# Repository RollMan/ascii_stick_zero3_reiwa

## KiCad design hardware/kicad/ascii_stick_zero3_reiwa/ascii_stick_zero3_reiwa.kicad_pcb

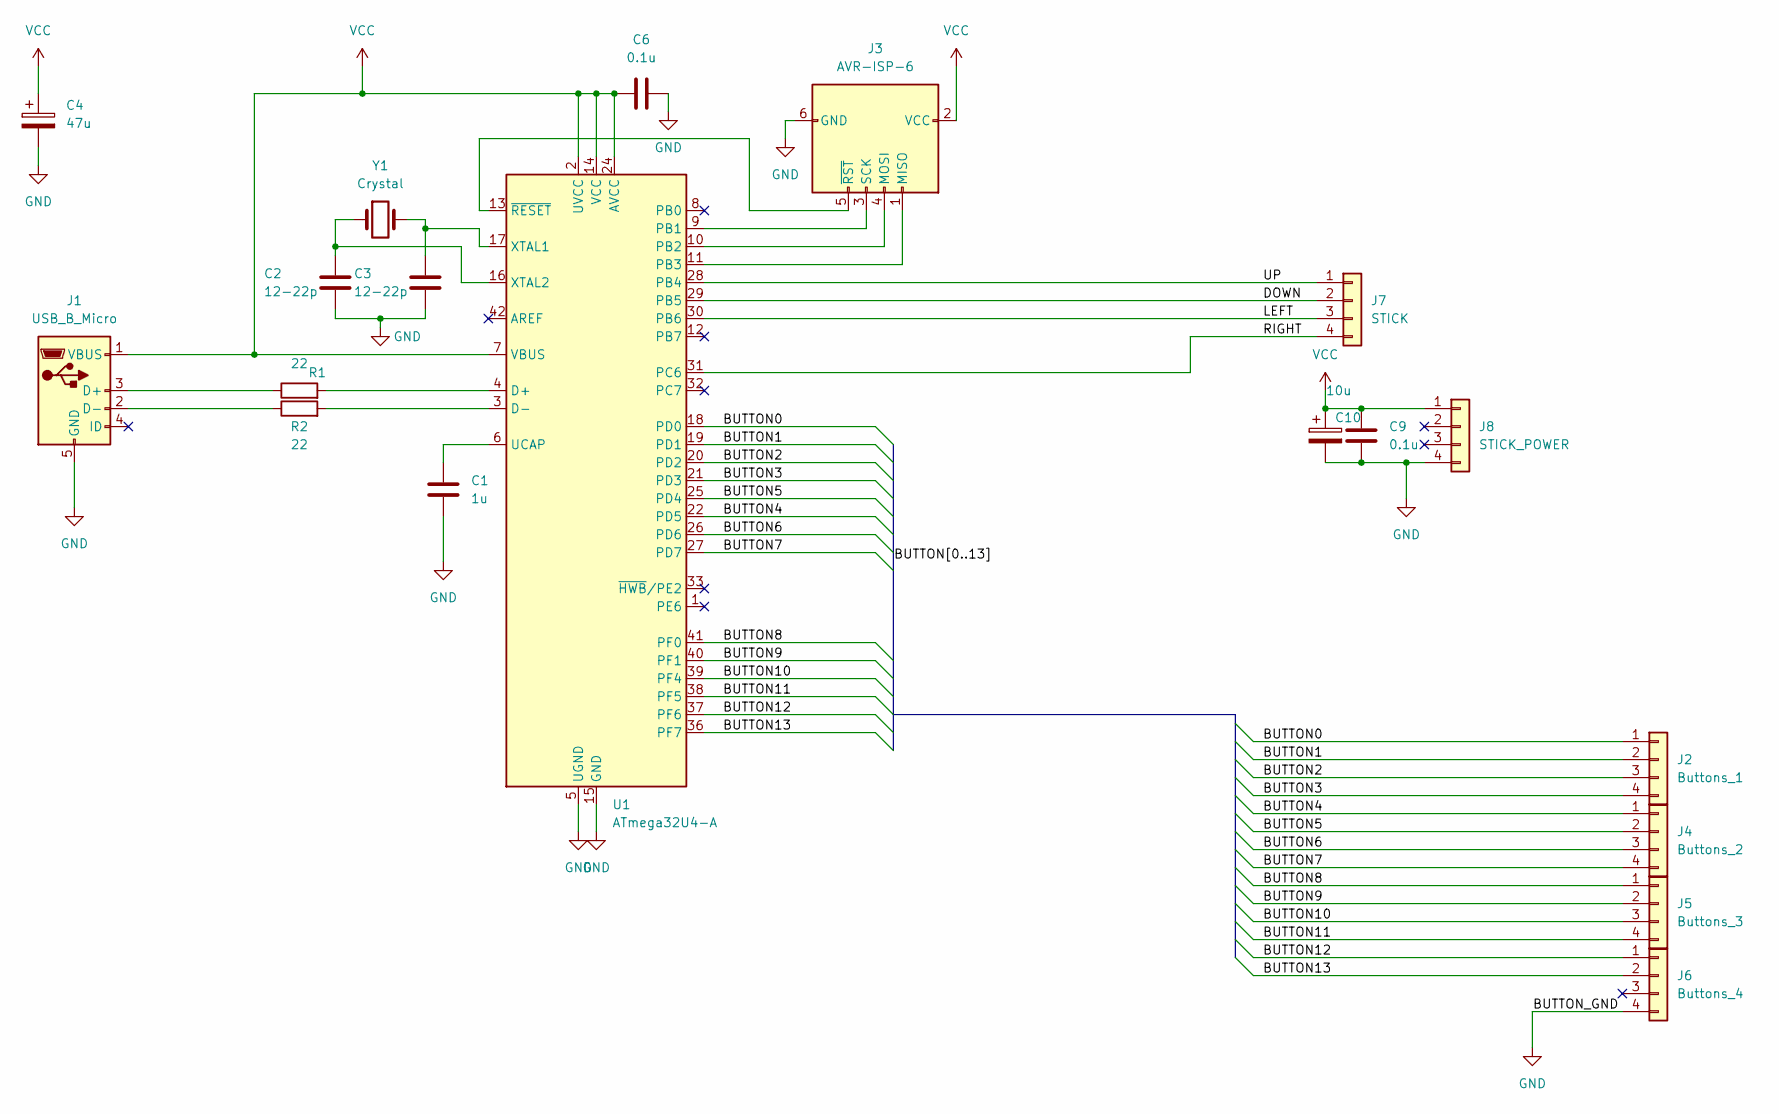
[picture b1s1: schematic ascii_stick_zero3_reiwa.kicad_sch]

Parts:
C1: 1u; C_Disc_D5.1mm_W3.2mm_P5.00mm
C2, C3: 12-22p; C_Disc_D5.0mm_W2.5mm_P2.50mm
C4: 47u; CP_Radial_D4.0mm_P1.50mm
C6, C9: 0.1u; C_Disc_D3.0mm_W2.0mm_P2.50mm
C10: 10u; CP_Radial_D4.0mm_P1.50mm
J1: USB_B_Micro; PinSocket_1x05_P2.54mm_Vertical
J2: Buttons_1; JST_XH_B4B-XH-AM_1x04_P2.50mm_Vertical
J3: AVR-ISP-6; PinHeader_2x03_P2.54mm_Vertical
J4: Buttons_2; JST_XH_B4B-XH-AM_1x04_P2.50mm_Vertical
J5: Buttons_3; JST_XH_B4B-XH-AM_1x04_P2.50mm_Vertical
J6: Buttons_4; JST_XH_B4B-XH-AM_1x04_P2.50mm_Vertical
J7: STICK; JST_XH_B4B-XH-AM_1x04_P2.50mm_Vertical
J8: STICK_POWER; JST_XH_B4B-XH-AM_1x04_P2.50mm_Vertical
R1, R2: 22; R_Axial_DIN0411_L9.9mm_D3.6mm_P12.70mm_Horizontal
U1: ATmega32U4-A; TQFP-44_10x10mm_P0.8mm
Y1: Crystal; Crystal_HC49-4H_Vertical

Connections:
/BUTTON0: J2.1, U1.18 (PD0)
/BUTTON1: J2.2, U1.19 (PD1)
/BUTTON2: J2.3, U1.20 (PD2)
/BUTTON3: J2.4, U1.21 (PD3)
/BUTTON4: J4.1, U1.22 (PD5)
/BUTTON5: J4.2, U1.25 (PD4)
/BUTTON6: J4.3, U1.26 (PD6)
/BUTTON7: J4.4, U1.27 (PD7)
/BUTTON8: J5.1, U1.41 (PF0)
/BUTTON9: J5.2, U1.40 (PF1)
/BUTTON10: J5.3, U1.39 (PF4)
/BUTTON11: J5.4, U1.38 (PF5)
/BUTTON12: J6.1, U1.37 (PF6)
/BUTTON13: J6.2, U1.36 (PF7)
/DOWN: J7.2, U1.29 (PB5)
/LEFT: J7.3, U1.30 (PB6)
/RIGHT: J7.4, U1.31 (PC6)
/UP: J7.1, U1.28 (PB4)
GND: C1.2, C2.2, C3.2, C4.2, C6.2, C9.2, C10.2, J1.5 (GND), J3.6 (GND), J6.4, J8.4, U1.5 (UGND), U1.15 (GND), U1.23 (GND), U1.35 (GND), U1.43 (GND)
unnamed: J1.3 (D+), R1.1
unnamed: J1.2 (D-), R2.1
unnamed: J3.1 (MISO), U1.11 (PB3)
unnamed: J3.4 (MOSI), U1.10 (PB2)
unnamed: J3.3 (SCK), U1.9 (PB1)
unnamed: J3.5 (~RST), U1.13 (~RESET)
unnamed: R1.2, U1.4 (D+)
unnamed: R2.2, U1.3 (D-)
unnamed: C1.1, U1.6 (UCAP)
unnamed: C3.1, U1.17 (XTAL1), Y1.2
unnamed: C2.1, U1.16 (XTAL2), Y1.1
VCC: C4.1, C6.1, C9.1, C10.1, J1.1 (VBUS), J3.2 (VCC), J8.1, U1.2 (UVCC), U1.7 (VBUS), U1.14 (VCC), U1.24 (AVCC), U1.34 (VCC), U1.44 (AVCC)

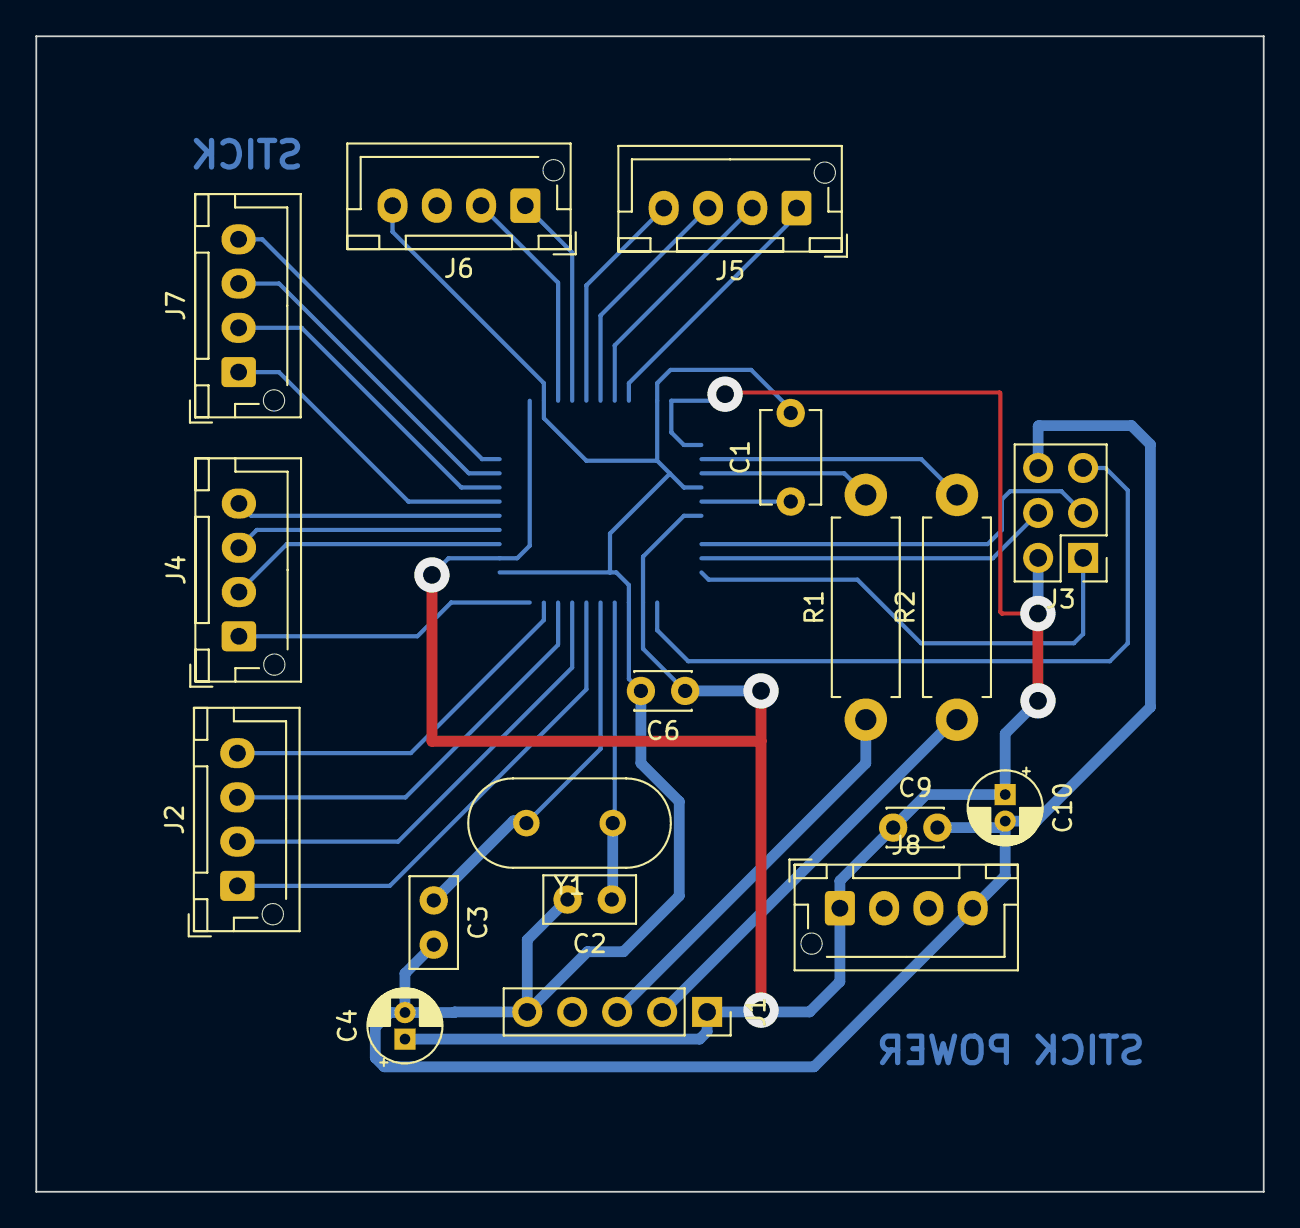
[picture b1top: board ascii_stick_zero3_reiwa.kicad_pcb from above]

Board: 2 copper layers, 69.3 x 65.3 mm, 19 parts (1 on the bottom side), 31 nets.

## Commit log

2024-02-11 for hand-etching
2024-02-11 follow jlcpcb constraints
2024-02-12 increase mergin of tracks from the MCU
2024-02-12 wip: add a build environment container for avr
2024-02-12 add a build environment as a prebuilt
2024-02-16 wip: configure PLL
2024-03-02 add some functional tests
2024-03-03 apply a workaround of a pagesize warning
    See https://gcc.gnu.org/bugzilla/show_bug.cgi?id=105523
2024-03-03 avoid the main function returns
2024-03-03 avoid sending from null packet pointer when standard request is invalid
2024-03-03 update gitignore
2024-03-03 add a macro to send a string without designation of its length
2024-03-03 add debug macros
2024-03-03 ok to send device descriptor
2024-03-03 restore device descriptor
2024-03-09 concatenate descriptors
2024-03-09 wip: try low speed to diagnostic circuit problem (parastic capacitance
2024-03-25 add a test that uses arduino instead of baremetal
